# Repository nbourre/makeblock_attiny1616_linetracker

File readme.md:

# Description

This project is to create a PCB which connects the MakeBlock Ranger to an Adafruit ATtiny1616 breakout which connects to an IR line sensor. The PCB will be used to feed the line sensor data to the Ranger.

## Schematic

## PCB

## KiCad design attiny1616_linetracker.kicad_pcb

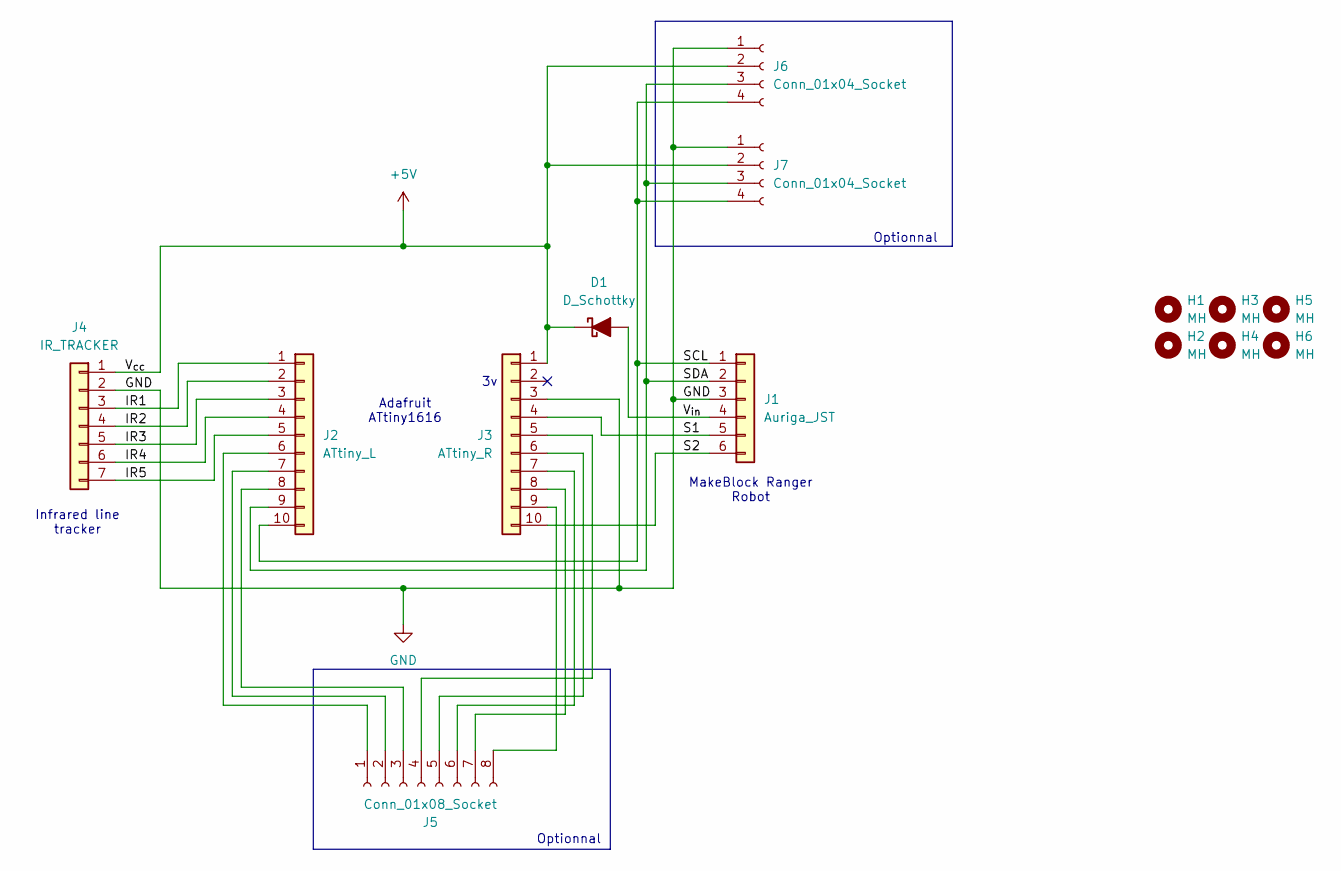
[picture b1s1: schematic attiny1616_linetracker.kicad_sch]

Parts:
D1: D_Schottky; D_SOD-123; LCSC C78545
H1, H2, H3, H4, H5, H6: MH; MountingHole_4.3mm_M4_Pad_TopBottom_MakeBlock
J1: Auriga_JST; JST_XH_S6B-XH-A-1_1x06_P2.50mm_Horizontal; LCSC C157919
J2: ATtiny_L; PinSocket_1x10_P2.54mm_Vertical; LCSC C2897373
J3: ATtiny_R; PinSocket_1x10_P2.54mm_Vertical; LCSC C2897373
J4: IR_TRACKER; JST_XH_B7B-XH-A_1x07_P2.50mm_Vertical; LCSC C6332200
J5: Conn_01x08_Socket; PinSocket_1x08_P2.54mm_Vertical; LCSC C27438
J6, J7: Conn_01x04_Socket; PinSocket_1x04_P2.54mm_GVSCLSDC; LCSC C2718488

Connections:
+5V: D1.1 (K), J3.1 (Vin), J4.1, J6.2, J7.2
/IR1: J2.1 (Pin_0), J4.3
/IR2: J2.2 (Pin_1), J4.4
/IR3: J2.3 (Pin_2), J4.5
/IR4: J2.4 (Pin_3), J4.6
/IR5: J2.5 (Pin_4), J4.7
/S1: J1.5 (S1), J3.4 (Pin_16)
/S2: J1.6 (S2), J3.10 (Pin_11)
/SCL: J1.1 (SCL), J2.10 (SCL), J6.4, J7.4
/SDA: J1.2 (SDA), J2.9 (SDA), J6.3, J7.3
/V_{in}: D1.2 (A), J1.4 (PWR_B)
GND: J1.3 (PWR_A), J3.3 (GND), J4.2, J6.1, J7.1
unnamed: J2.6 (Pin_5), J5.1
unnamed: J2.7 (RXD), J5.2
unnamed: J2.8 (TXD), J5.3
unnamed: J3.9 (Pin_12), J5.8
unnamed: J3.8 (Pin_13), J5.7
unnamed: J3.6 (Pin_14), J5.5
unnamed: J3.5 (Pin_15), J5.4
unnamed: J3.7 (UPDI), J5.6

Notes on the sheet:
Optionnal
MakeBlock Ranger Robot
Adafruit ATtiny1616
Infrared line tracker

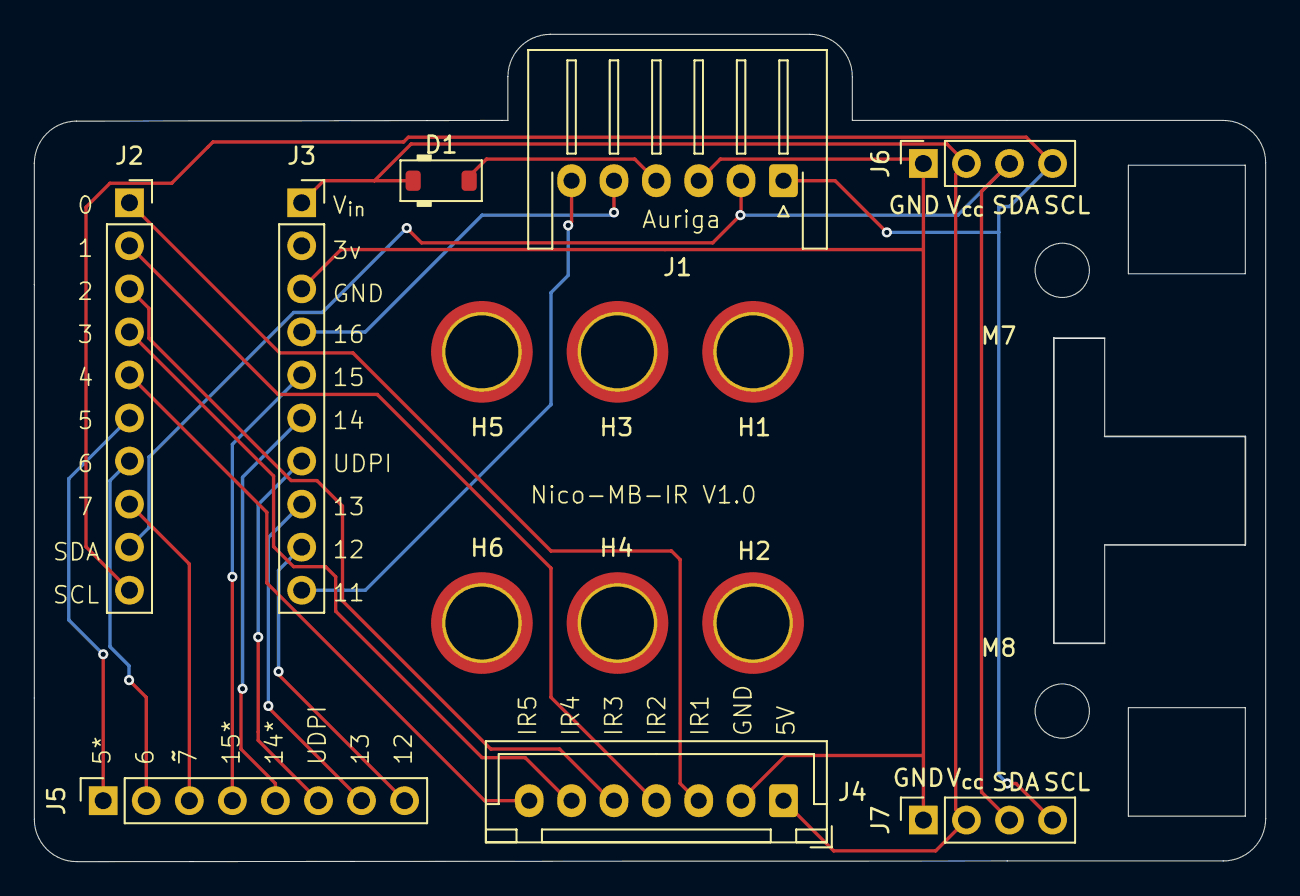
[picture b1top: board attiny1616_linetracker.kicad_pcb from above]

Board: 2 copper layers, 72.6 x 48.8 mm, 16 parts (0 on the bottom side), 20 nets.

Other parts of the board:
M7, M8: MountingHole_3.2mm_M3

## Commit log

2024-09-05 Modified gitignore
2024-09-05 Added image to readme
2024-09-05 Removed fp-info-cache
2024-09-05 Updated gitignore
2024-09-05 Preproduction
